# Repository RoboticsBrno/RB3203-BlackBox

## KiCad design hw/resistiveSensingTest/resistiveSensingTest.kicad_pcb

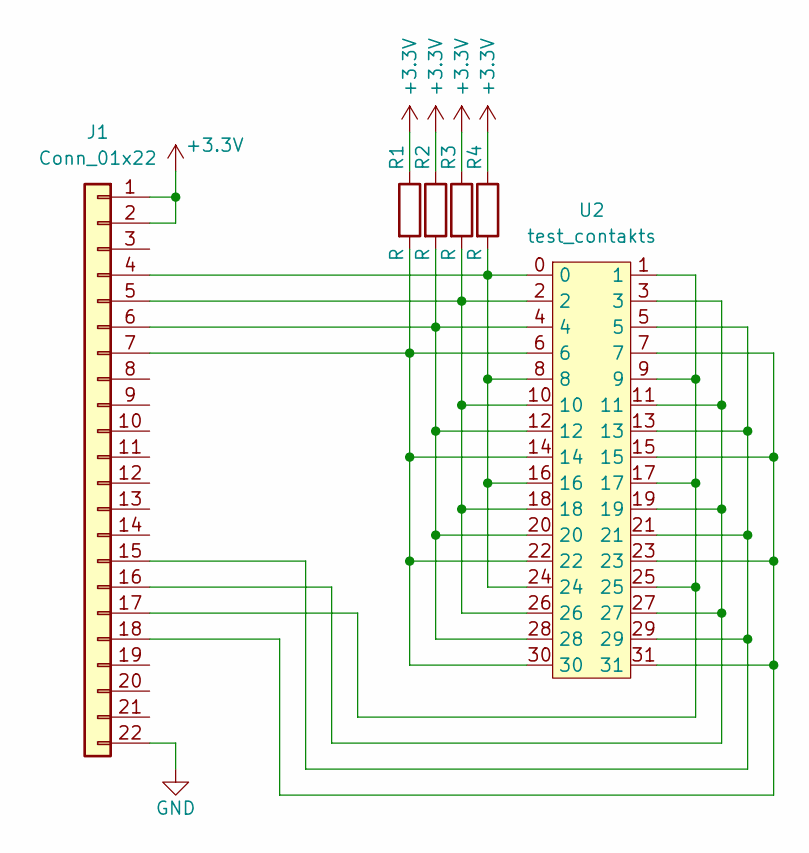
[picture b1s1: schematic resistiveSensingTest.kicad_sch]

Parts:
J1: Conn_01x22; PinHeader_1x22_P2.54mm_Vertical
R1, R2, R3, R4: R; R_1206_3216Metric_Pad1.30x1.75mm_HandSolder
U2: test_contakts

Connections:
+3.3V: J1.1, J1.2, R1.1, R2.1, R3.1, R4.1
GND: J1.22
unnamed: J1.7, R1.2, U2.6, U2.14, U2.22, U2.30
unnamed: J1.6, R2.2, U2.4, U2.12, U2.20, U2.28
unnamed: J1.5, R3.2, U2.2, U2.10, U2.18, U2.26
unnamed: J1.4, R4.2, U2.0, U2.8, U2.16, U2.24
unnamed: J1.17, U2.1, U2.9, U2.17, U2.25
unnamed: J1.16, U2.3, U2.11, U2.19, U2.27
unnamed: J1.15, U2.5, U2.13, U2.21, U2.29
unnamed: J1.18, U2.7, U2.15, U2.23, U2.31

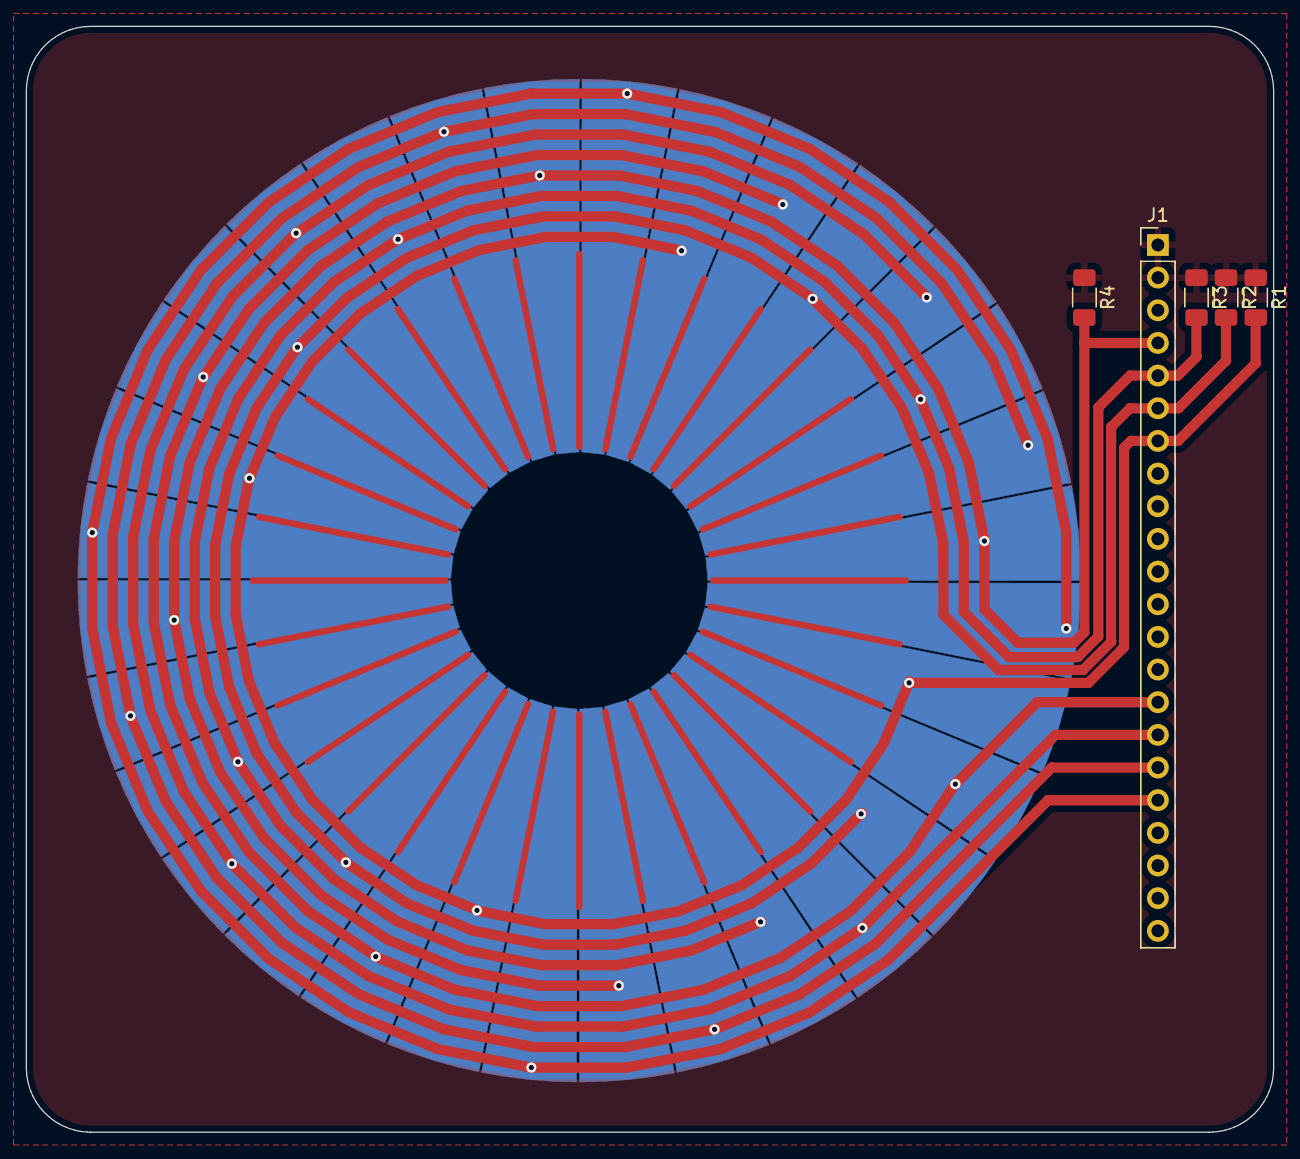
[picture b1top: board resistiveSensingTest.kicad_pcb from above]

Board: 2 copper layers, 97.0 x 86.0 mm, 6 parts (1 on the bottom side), 9 nets.

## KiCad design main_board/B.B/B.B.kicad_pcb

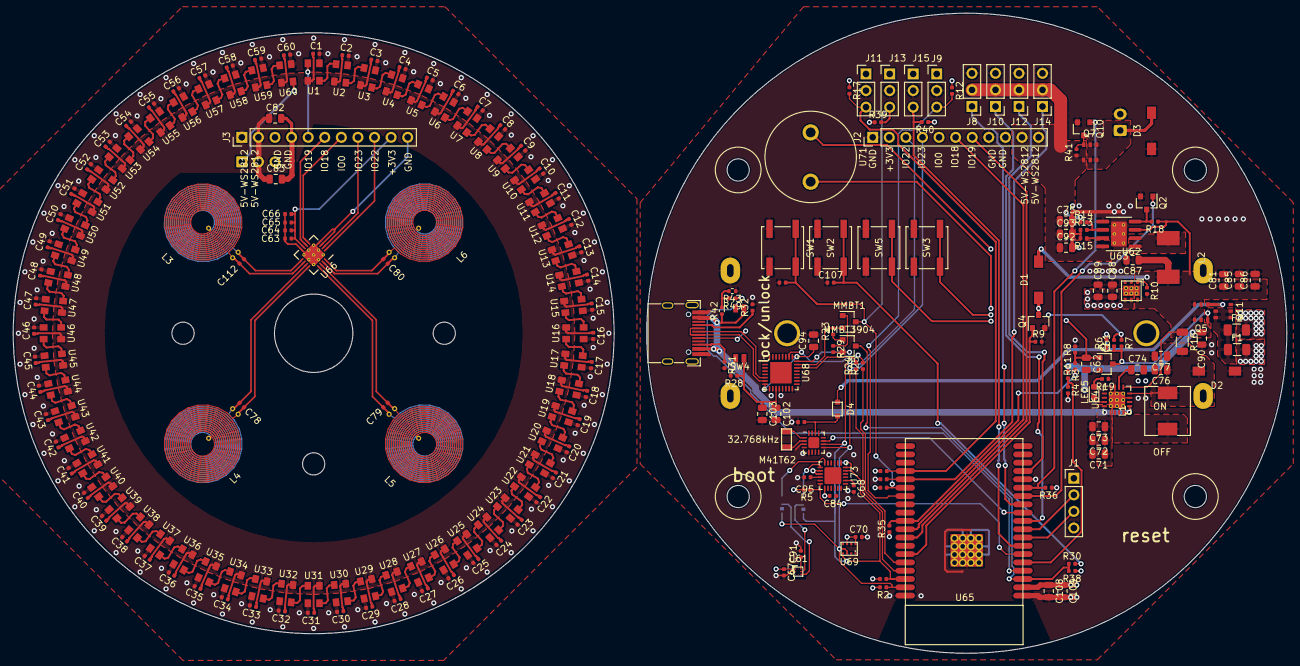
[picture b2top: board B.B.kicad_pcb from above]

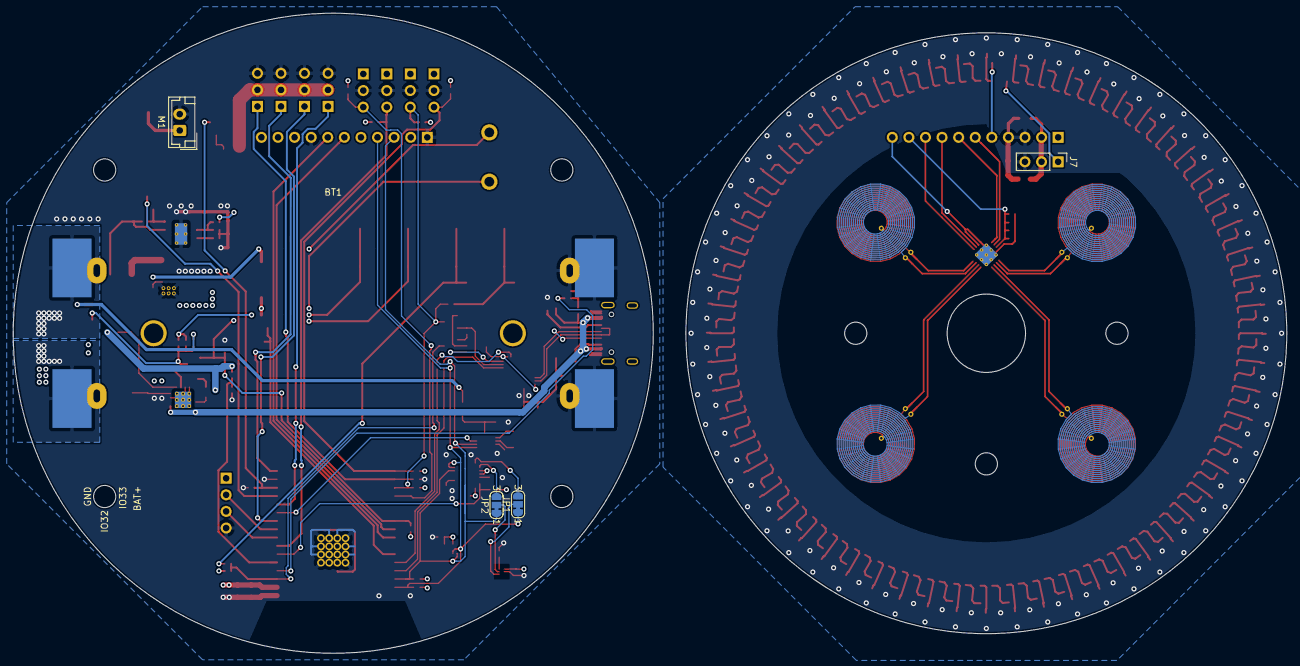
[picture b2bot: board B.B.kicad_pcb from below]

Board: 4 copper layers, 195.0 x 98.0 mm, 258 parts (5 on the bottom side), 152 nets.

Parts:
BT1: Battery_Cell; 18650-holder
C1, C2, C3, C4, C5, C6, C7, C8, C9, C10, C11, C12, C13, C14, C15, C16, C17, C18, C19, C20, C21, C22, C23, C24, C25, C26, C27, C28, C29, C30, C31, C32, C33, C34, C35, C36, C37, C38, C39, C40, C41, C42, C43, C44, C45, C46, C47, C48, C49, C50, C51, C52, C53, C54, C55, C56, C57, C58, C59, C60: 220nf; C_0402_1005Metric
C61, C66: 1uf; C_0402_1005Metric
C62, C89: 2.2uf; C_0805_2012Metric
C63, C64: 10nf; C_0402_1005Metric
C65, C95: 0.1uf; R_0402_1005Metric
C67, C68: 2.2uf; C_0402_1005Metric
C69, C70, C84: 1uf; R_0402_1005Metric
C71, C72, C73, C75, C86, C90, C92, C93: 22uf; C_0805_2012Metric
C74, C76, C81, C94, C102, C108: 0.1uf; C_0805_2012Metric
C77, C82, C83, C85, C88, C103, C109: 10uf; C_0805_2012Metric
C78, C79, C80, C112: 1000pf; C_0402_1005Metric
C87: 4.7uf; C_0805_2012Metric
C91: 4.7uf; C_0402_1005Metric
C104, C107: 100nf; C_0402_1005Metric
D1, D2, D3: SS54; DO-214AC
D4: D; SOD-323
F1, F2: Polyfuse; L_1206_3216Metric
J1: Conn_01x04; PinHeader_1x04_P2.54mm_Vertical
J2, J3: Conn_01x11; PinHeader_1x11_P2.54mm_Vertical
J5: USB_C_Receptacle_USB2.0; USB_C_Female-16Pin-HPJF
J7, J8, J9, J10, J11, J12, J13, J14, J15: Conn_01x03; PinHeader_1x03_P2.54mm_Vertical
JP1, JP2: Jumper_NC_Dual; SolderJumper-3_P1.3mm_Bridged12_RoundedPad1.0x1.5mm_NumberL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
L1: 22u; SL00630H
L2: 2.2uH; MWSA0603_6.6x7.1x3.0
L3, L4, L5, L6: L; coil
LED5: BLUE; LED_0603_1608Metric
M1: Motor_DC; JST_EH_B2B-EH-A_1x02_P2.50mm_Vertical
MMBT1, MMBT3904: Q_NPN_BCE; SOT-23
Q1, Q2, Q4, Q10: 2N7002; SOT-23
Q5, Q7, Q11: SI3447CDV; TSOP-6_1.5x3.0x0.95P
R1, R2, R13, R43: 7.5k; R_0402_1005Metric
R3, R7, R8, R28: 1M; R_0402_1005Metric
R4: 300k; C_0402_1005Metric
R5, R12, R17, R23, R29, R33, R34, R35, R36, R37, R38, R39, R40: 12k; R_0402_1005Metric
R6, R10, R18, R41: 100k; R_0402_1005Metric
R9: 47k; R_0402_1005Metric
R11, R24, R25, R49: 220; R_0402_1005Metric
R14, R15: 56k; R_0402_1005Metric
R16: 75m; R_1206_3216Metric
R19: 1k; R_0402_1005Metric
R20, R30: 470; R_0402_1005Metric
R31, R32, R42: 5.1k; R_0402_1005Metric
SW1, SW2, SW3, SW5: SW_DIP_x01; SW_Push_1P1T_NO_CK_KSC6xxJ
SW4: SW_DIP_x02; SW-SMD-4
U1, U2, U3, U4, U5, U6, U7, U8, U9, U10, U11, U12, U13, U14, U15, U16, U17, U18, U19, U20, U21, U22, U23, U24, U25, U26, U27, U28, U29, U30, U31, U32, U33, U34, U35, U36, U37, U38, U39, U40, U41, U42, U43, U44, U45, U46, U47, U48, U49, U50, U51, U52, U53, U54, U55, U56, U57, U58, U59, U60: WS2812
U61: QMC6310
U62: NCP708; UDFN6_3x3
U63: FP6276; SOIC-8-1EP_3.9x4.9mm_P1.27mm_EP2.41x3.81mm_ThermalVias
U64: TP5100; QFN-16-1EP_4x4mm_P0.65mm_EP2.5x2.5mm_ThermalVias
U65: ESP32-WROVER
U66: LDC1314; WQFN-16-1EP_4x4mm_P0.5mm_EP2.6x2.6mm_ThermalVias
U67: M41T62; QFN-16-1EP_3x3mm_P0.5mm_EP1.7x1.7mm
U68: FT232RQ; QFN-32-1EP_5x5mm_P0.5mm_EP3.3x3.3mm
U69: SPL06; SMD-8_2x2.5x0.65P
U71: piezo
U73: MPU6050; QFN-24-1EP_4x4mm_P0.5mm_EP2.6x2.6mm
Y1: 32.768kHz; SMD-3215_2P

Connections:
+3V3: C67.1, C70.1, C84.1, C88.1, C89.1, C108.1, C109.1, J2.2, J9.1, J11.1, J13.1, J15.1, R1.2, R2.2, R5.2, R12.1, R17.1, R33.1, R35.1, R37.1, R38.1, R39.1, R40.1, U61.A1, U62.4, U62.5, U65.2, U69.6, U69.8, U73.8, U73.9, U73.13
+5V: C75.1, C92.1, C93.1, J2.10, J2.11, J8.2, J10.2, J12.2, J14.2, Q7.4, R14.1, R41.1, U63.8
/BAT+: D4.2, Q5.4, Q11.4, R6.2
/ESP3200/D+: J5.A6, J5.B6, U68.14
/ESP3200/D-: J5.A7, J5.B7, U68.15
/ESP3200/DTR: MMBT1.2, R23.2, U68.31
/ESP3200/EN: MMBT3904.3, R30.1, R38.2, U65.3
/ESP3200/IO0-up: J13.3, MMBT1.3, R20.1, R33.2, R39.2, U65.25
/ESP3200/IO2-down: J14.1, R34.2, U65.24
/ESP3200/IO4: J9.3, R12.2, U65.26
/ESP3200/IO5-up: R11.1, R35.2, U65.29
/ESP3200/IO12-down: Q10.1, R36.2, U65.14
/ESP3200/IO13: J12.1, U65.16
/ESP3200/IO14: Q2.1, U65.13
/ESP3200/IO15-up: J11.3, R17.2, R37.2, U65.23
/ESP3200/IO18: J2.6, U65.30
/ESP3200/IO19: J2.7, U65.31
/ESP3200/IO21: Q4.1, R9.1, U65.33
/ESP3200/IO22: J2.3, JP2.1, R1.1, U65.36, U67.10, U69.4, U73.23
/ESP3200/IO23: J2.4, JP1.1, R2.1, U65.37, U67.9, U69.3, U73.24
/ESP3200/IO25: J10.1, U65.10
/ESP3200/IO26: U65.11, U67.11
/ESP3200/IO27: J8.1, U65.12
/ESP3200/IO34: R5.1, U65.6, U73.12
/ESP3200/IO35: J15.3, R40.2, U65.7
/ESP3200/IO36: R49.1, U65.4
/ESP3200/IO39: R3.2, R4.1, U65.5
/ESP3200/RTS: MMBT3904.2, R29.2, U68.32
/ESP3200/RX-esp: R25.1, U65.34
/ESP3200/TX-esp: R24.1, U65.35
/expanz00/A9-RX: J1.3, U65.8
/expanz00/A9-TX: J1.2, U65.9
/next-board00/3V3: C63.1, C64.1, C65.1, C66.2, J3.10, U66.7
/next-board00/5V: C1.2, C2.2, C3.2, C4.2, C5.2, C6.2, C7.2, C8.2, C9.2, C10.2, C11.2, C12.2, C13.2, C14.2, C15.2, C16.2, C17.2, C18.2, C19.2, C20.2, C21.2, C22.2, C23.2, C24.2, C25.2, C26.2, C27.2, C28.2, C29.2, C30.2, C31.2, C32.2, C33.2, C34.2, C35.2, C36.2, C37.2, C38.2, C39.2, C40.2, C41.2, C42.2, C43.2, C44.2, C45.2, C46.2, C47.2, C48.2, C49.2, C50.2, C51.2, C52.2, C53.2, C54.2, C55.2, C56.2, C57.2, C58.2, C59.2, C60.2, C82.1, C83.1, J3.1, J3.2, J7.2, U1.1, U2.1, U3.1, U4.1, U5.1, U6.1, U7.1, U8.1, U9.1, U10.1, U11.1, U12.1, U13.1, U14.1, U15.1, U16.1, U17.1, U18.1, U19.1, U20.1, U21.1, U22.1, U23.1, U24.1, U25.1, U26.1, U27.1, U28.1, U29.1, U30.1, U31.1, U32.1, U33.1, U34.1, U35.1, U36.1, U37.1, U38.1, U39.1, U40.1, U41.1, U42.1, U43.1, U44.1, U45.1, U46.1, U47.1, U48.1, U49.1, U50.1, U51.1, U52.1, U53.1, U54.1, U55.1, U56.1, U57.1, U58.1, U59.1, U60.1
/next-board00/GND: C1.1, C2.1, C3.1, C4.1, C5.1, C6.1, C7.1, C8.1, C9.1, C10.1, C11.1, C12.1, C13.1, C14.1, C15.1, C16.1, C17.1, C18.1, C19.1, C20.1, C21.1, C22.1, C23.1, C24.1, C25.1, C26.1, C27.1, C28.1, C29.1, C30.1, C31.1, C32.1, C33.1, C34.1, C35.1, C36.1, C37.1, C38.1, C39.1, C40.1, C41.1, C42.1, C43.1, C44.1, C45.1, C46.1, C47.1, C48.1, C49.1, C50.1, C51.1, C52.1, C53.1, C54.1, C55.1, C56.1, C57.1, C58.1, C59.1, C60.1, C82.2, C83.2, J3.3, J3.4, J7.3, U1.3, U2.3, U3.3, U4.3, U5.3, U6.3, U7.3, U8.3, U9.3, U10.3, U11.3, U12.3, U13.3, U14.3, U15.3, U16.3, U17.3, U18.3, U19.3, U20.3, U21.3, U22.3, U23.3, U24.3, U25.3, U26.3, U27.3, U28.3, U29.3, U30.3, U31.3, U32.3, U33.3, U34.3, U35.3, U36.3, U37.3, U38.3, U39.3, U40.3, U41.3, U42.3, U43.3, U44.3, U45.3, U46.3, U47.3, U48.3, U49.3, U50.3, U51.3, U52.3, U53.3, U54.3, U55.3, U56.3, U57.3, U58.3, U59.3, U60.3
/next-board00/INT: J3.7, U66.5
/next-board00/LDC-GND: C63.2, C64.2, C65.2, C66.1, J3.11, U66.3, U66.4, U66.8, U66.17
/next-board00/SCL: J3.9, U66.1
/next-board00/SDA: J3.8, U66.2
/next-board00/SHUTDOWN: J3.6, U66.6
/next-board00/WS2812: J3.5, U1.4
/next-board00/WS281200/0-8: U8.2, U9.4
/next-board00/WS281200/1-8: U16.2, U17.4
/next-board00/WS281200/2-8: U24.2, U25.4
/next-board00/WS281200/3-8: U32.2, U33.4
/next-board00/WS281200/4-8: U40.2, U41.4
/next-board00/WS281200/5-8: U48.2, U49.4
/next-board00/WS281200/6-8: U56.2, U57.4
/next-board00/WS281200/DOUT: J7.1, U60.2
GND: BT1.2, BT1.4, C62.2, C67.2, C68.2, C69.2, C70.2, C71.2, C72.2, C73.2, C74.2, C75.2, C76.2, C77.2, C81.2, C84.2, C85.2, C86.2, C87.2, C88.2, C89.2, C90.2, C91.2, C92.2, C93.2, C94.2, C95.2, C102.2, C103.2, C104.1, C107.1, C108.2, C109.2, D2.2, D3.2, J1.4, J2.1, J2.8, J2.9, J5.A1, J5.A12, J5.B1, J5.B12, J8.3, J9.2, J10.3, J11.2, J12.3, J13.2, J14.3, J15.2, M1.2, Q1.2, Q2.2, Q4.2, Q10.2, Q11.3, R4.2, R8.2, R9.2, R13.1, R15.2, R19.1, R28.2, R31.2, R32.2, R34.1, R36.1, R43.1, SW1.1, SW2.1, SW3.1, SW5.1, U61.B1, U62.2, U62.7, U63.5, U63.9, U64.7, U64.11, U64.12, U64.17, U65.1, U65.15, U65.38, U65.39, U67.3, U67.5, U68.4, U68.17, U68.20, U68.24, U68.26, U69.1, U69.7, U73.1, U73.11, U73.18
LX: L2.2, U63.1, U63.2
unnamed: BT1.1, F2.2
unnamed: BT1.3, F1.2
unnamed: C61.1, Q1.3, Q5.3, R6.1, R7.2
unnamed: C61.2, R7.1, SW3.2
unnamed: C62.1, Q1.1, R8.1, R11.2, SW5.2
unnamed: C68.1, U73.20
unnamed: C69.1, D4.1, U67.14
unnamed: C74.1, U64.10
unnamed: C76.1, C77.1, D2.1, L1.2, R16.2, U64.8
unnamed: C78.1, L4.1, U66.12
unnamed: C78.2, L4.2, U66.11
unnamed: C79.1, L5.1, U66.14
unnamed: C79.2, L5.2, U66.13
unnamed: C80.1, L6.1, U66.16
unnamed: C80.2, L6.2, U66.15
unnamed: C91.1, U61.A3
unnamed: C94.1, U68.1, U68.16
unnamed: C95.1, U73.10
unnamed: C102.1, C103.1, R28.1, SW4.3, U68.19
unnamed: C104.2, R20.2, SW1.2
unnamed: C107.2, R30.2, SW2.2
unnamed: C112.1, L3.1, U66.10
unnamed: C112.2, L3.2, U66.9
unnamed: D1.2, Q4.3, U71.1
unnamed: D3.1, M1.1, Q7.1, Q7.2, Q7.5, Q7.6
unnamed: F1.1, F2.1, Q11.1, Q11.2, Q11.5, Q11.6
unnamed: J5.A5, R32.1
unnamed: J5.B5, R31.1
unnamed: JP1.2, U61.C3
unnamed: JP1.3, U73.6
unnamed: JP2.2, U61.B3
unnamed: JP2.3, U73.7
unnamed: L1.1, U64.2, U64.3
unnamed: LED5.1, U64.15
unnamed: LED5.2, R19.2
unnamed: MMBT1.1, R29.1
unnamed: MMBT3904.1, R23.1
unnamed: Q2.3, R18.2, U63.4
unnamed: Q7.3, Q10.3, R41.2
unnamed: R10.1, U62.1
unnamed: R13.2, R14.2, U63.6
unnamed: R15.1, U63.7
unnamed: R24.2, U68.30
unnamed: R25.2, U68.2
unnamed: R42.2, R43.2, R49.2
unnamed: U1.2, U2.4
unnamed: U2.2, U3.4
unnamed: U3.2, U4.4
unnamed: U4.2, U5.4
unnamed: U5.2, U6.4
unnamed: U6.2, U7.4
unnamed: U7.2, U8.4
unnamed: U10.2, U11.4
unnamed: U9.2, U10.4
unnamed: U11.2, U12.4
unnamed: U12.2, U13.4
unnamed: U13.2, U14.4
unnamed: U14.2, U15.4
unnamed: U15.2, U16.4
unnamed: U17.2, U18.4
unnamed: U18.2, U19.4
unnamed: U19.2, U20.4
unnamed: U20.2, U21.4
unnamed: U21.2, U22.4
unnamed: U22.2, U23.4
unnamed: U23.2, U24.4
unnamed: U25.2, U26.4
unnamed: U26.2, U27.4
unnamed: U27.2, U28.4
unnamed: U28.2, U29.4
unnamed: U29.2, U30.4
unnamed: U30.2, U31.4
unnamed: U31.2, U32.4
unnamed: U33.2, U34.4
unnamed: U34.2, U35.4
unnamed: U35.2, U36.4
unnamed: U36.2, U37.4
unnamed: U37.2, U38.4
unnamed: U38.2, U39.4
unnamed: U39.2, U40.4
unnamed: U41.2, U42.4
unnamed: U42.2, U43.4
unnamed: U43.2, U44.4
unnamed: U44.2, U45.4
unnamed: U45.2, U46.4
unnamed: U46.2, U47.4
unnamed: U47.2, U48.4
unnamed: U49.2, U50.4
unnamed: U50.2, U51.4
unnamed: U51.2, U52.4
unnamed: U52.2, U53.4
unnamed: U53.2, U54.4
unnamed: U54.2, U55.4
unnamed: U55.2, U56.4
unnamed: U57.2, U58.4
unnamed: U58.2, U59.4
unnamed: U59.2, U60.4
unnamed: U67.1, Y1.1
unnamed: U67.2, Y1.2
VCC: C81.1, C85.1, C86.1, C87.1, C90.1, D1.1, J1.1, L2.1, Q5.1, Q5.2, Q5.5, Q5.6, R3.1, R10.2, R16.1, R18.1, U62.6, U63.3, U64.9, U71.2
VIN: C71.1, C72.1, C73.1, J5.A4, J5.A9, J5.B4, J5.B9, R42.1, SW4.2, U64.1, U64.4, U64.5, U64.16

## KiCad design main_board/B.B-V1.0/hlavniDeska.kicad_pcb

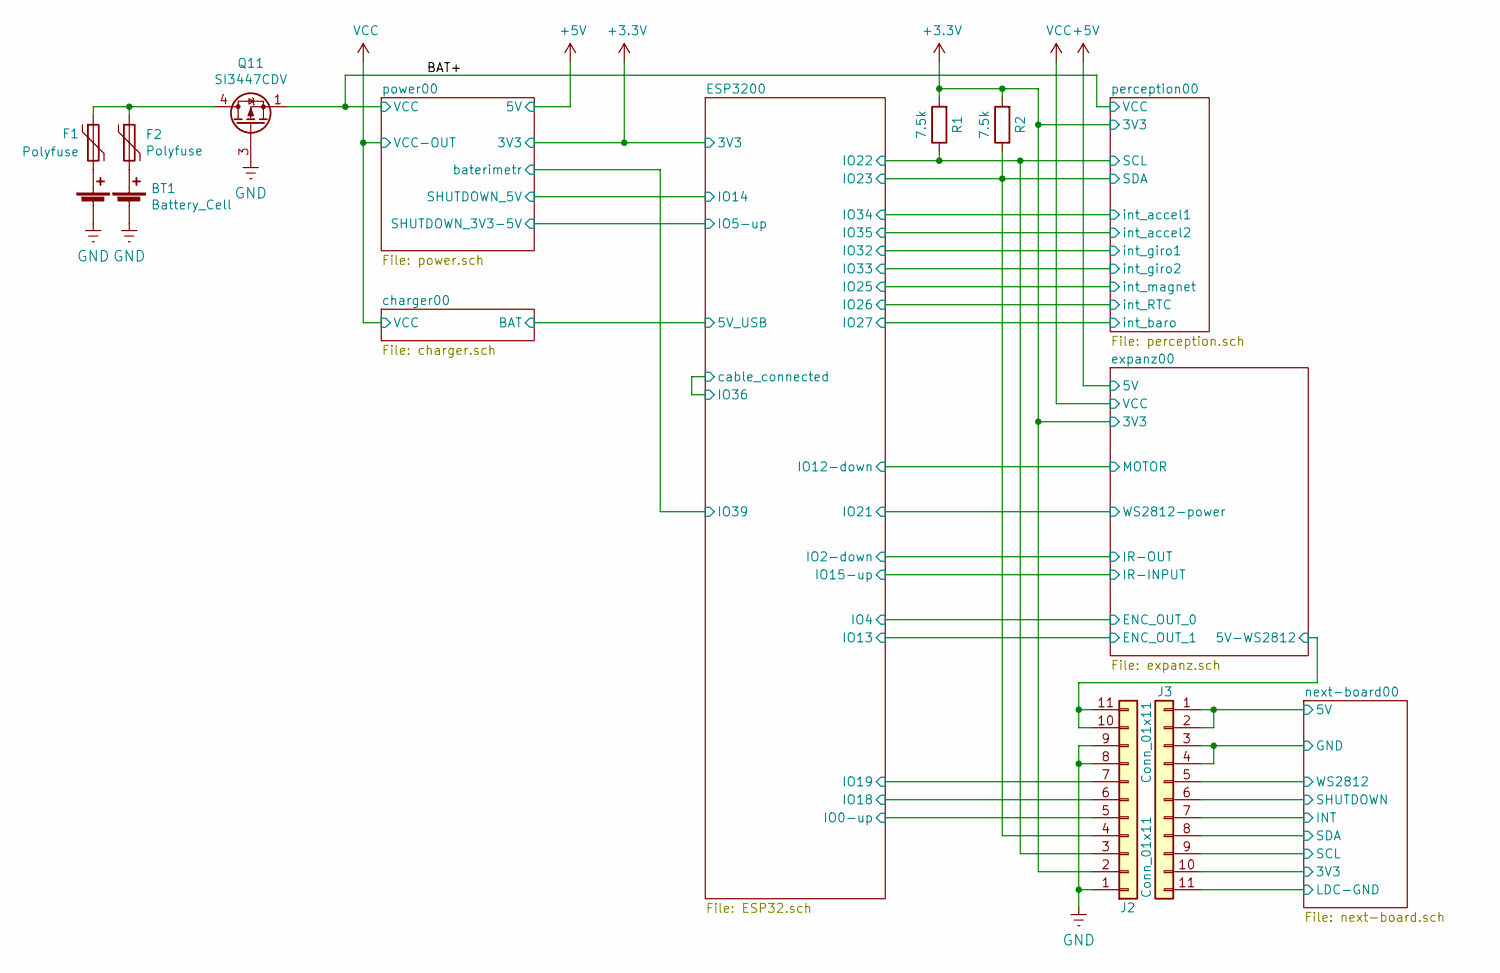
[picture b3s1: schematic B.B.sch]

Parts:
BT1: Battery_Cell; 18650-holder
F1, F2: Polyfuse; L_1206_3216Metric; LCSC C20988
J2, J3: Conn_01x11; PinHeader_1x11_P2.54mm_Vertical
Q11: SI3447CDV; TSOP-6_1.5x3.0x0.95P; LCSC C144884
R1, R2: 7.5k; R_0402_1005Metric; LCSC C25918

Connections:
+3V3: J2.2, R1.2, R2.2; also elsewhere on the board
/BAT+: Q11.1 (S), Q11.2, Q11.5, Q11.6; also elsewhere on the board
/ESP3200/IO0-up: J2.5; also elsewhere on the board
/ESP3200/IO18: J2.6; also elsewhere on the board
/ESP3200/IO19: J2.7; also elsewhere on the board
/ESP3200/IO22: J2.3, R1.1; also elsewhere on the board
/ESP3200/IO23: J2.4, R2.1; also elsewhere on the board
/expanz00/5V-WS2812: J2.10, J2.11; also elsewhere on the board
GND: BT1.2 (-), BT1.4 (-), J2.1, J2.8, J2.9, Q11.3 (G); also elsewhere on the board
unnamed: BT1.1 (+), F2.2
unnamed: BT1.3 (+), F1.2
unnamed: F1.1, F2.1, Q11.4 (D)
unnamed: J3.1, J3.2
unnamed: J3.3, J3.4

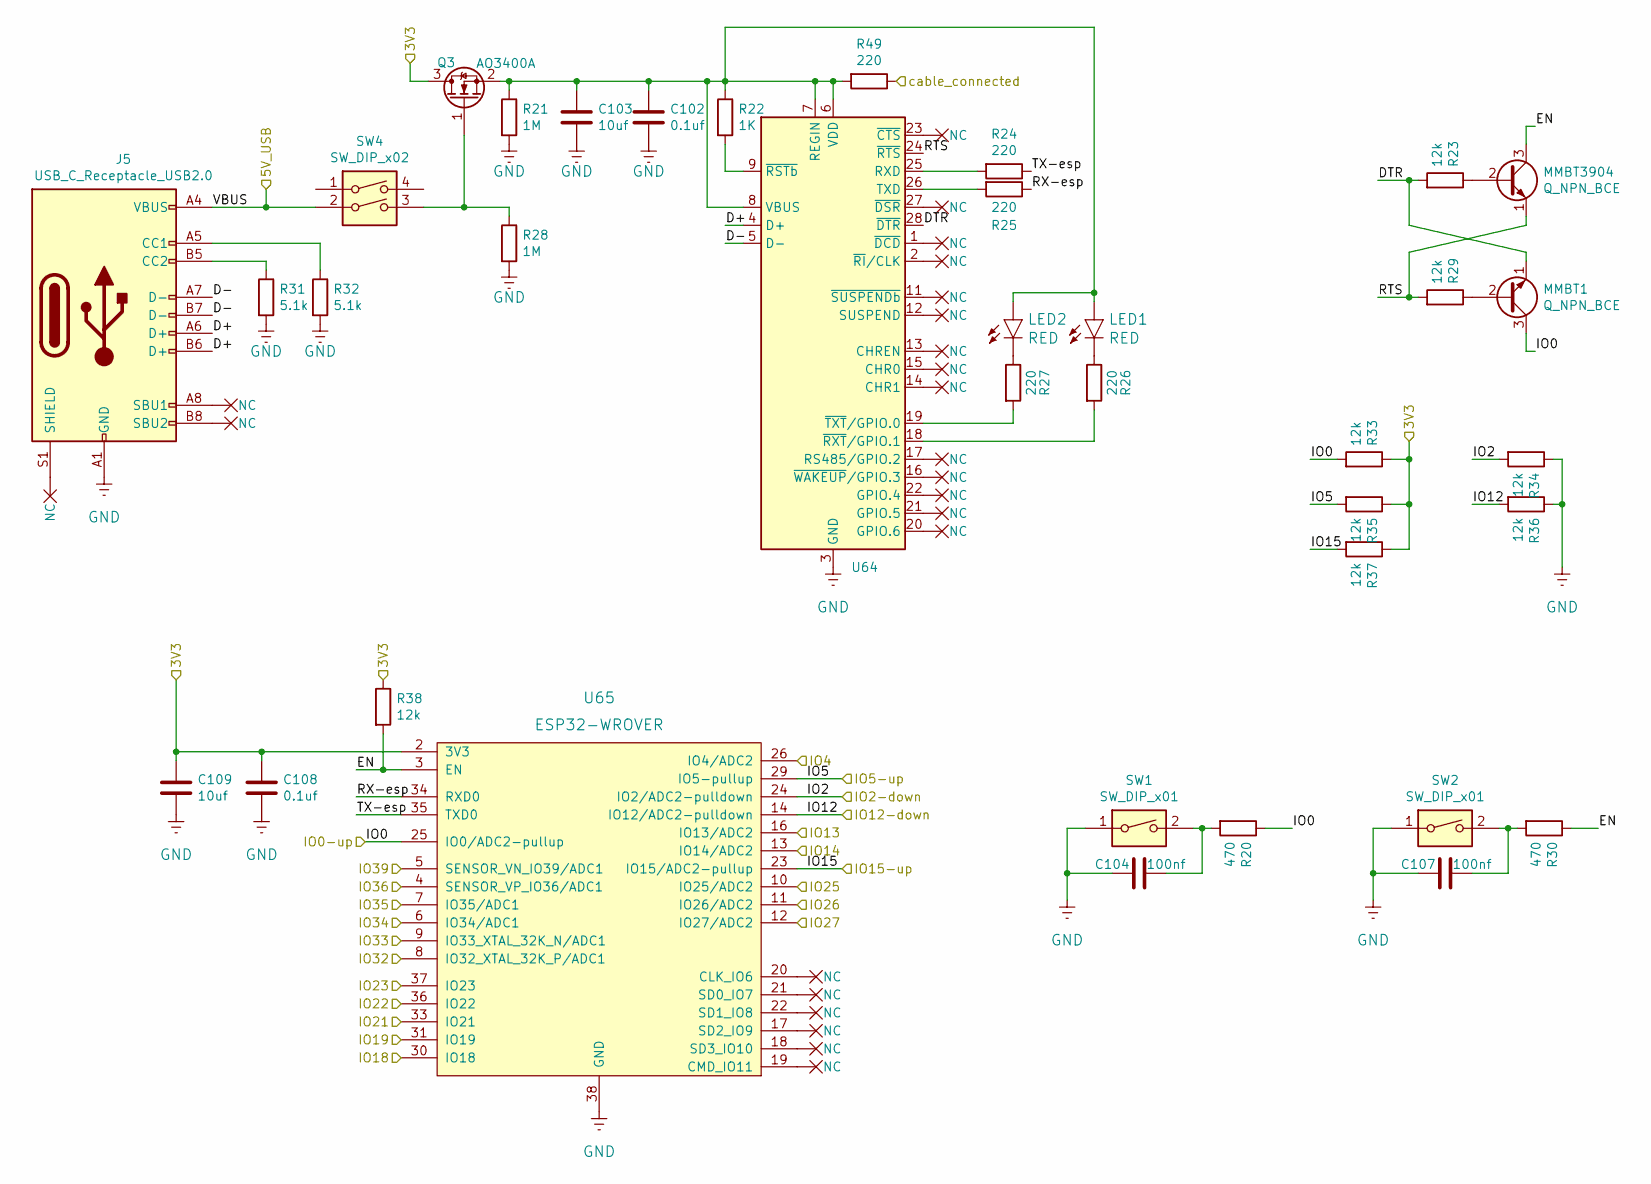
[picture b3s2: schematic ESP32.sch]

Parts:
C102, C108: 0.1uf; C_0805_2012Metric; LCSC C49678
C103, C109: 10uf; C_0805_2012Metric; LCSC C15850
C104, C107: 100nf; C_0402_1005Metric; LCSC C1525
J5: USB_C_Receptacle_USB2.0; USB_C_Female-16Pin-HPJF
LED1, LED2: RED; LED_0603_1608Metric; LCSC C2286
MMBT1, MMBT3904: Q_NPN_BCE; SOT-23; LCSC C20526
Q3: AO3400A; SOT-23; LCSC C20917
R20, R30: 470; R_0402_1005Metric; LCSC C25117
R21, R28: 1M; R_0402_1005Metric; LCSC C26083
R22: 1K; R_0402_1005Metric; LCSC C11702
R23, R29, R33, R34, R35, R36, R37, R38: 12k; R_0402_1005Metric; LCSC C25752
R24, R25, R26, R27, R49: 220; R_0402_1005Metric; LCSC C25092
R31, R32: 5.1k; R_0402_1005Metric; LCSC C25905
SW1, SW2: SW_DIP_x01; SW_Push_1P1T_NO_CK_KSC6xxJ; LCSC C318889
SW4: SW_DIP_x02; SW-SMD-4; LCSC C319052
U64: CP2102N-A01-GQFN28; QFN-28-1EP_5x5mm_P0.5mm_EP3.35x3.35mm; LCSC C105167
U65: ESP32-WROVER; LCSC C503591

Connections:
+3V3: C108.1, C109.1, Q3.3 (D), R33.1, R35.1, R37.1, R38.1, U65.2 (3V3); also elsewhere on the board
/ESP3200/5V_USB: J5.A4 (VBUS), J5.A9 (VBUS), J5.B4 (VBUS), J5.B9 (VBUS), SW4.2; also elsewhere on the board
/ESP3200/D+: J5.A6 (D+), J5.B6 (D+), U64.4 (D+)
/ESP3200/D-: J5.A7 (D-), J5.B7 (D-), U64.5 (D-)
/ESP3200/DTR: MMBT1.1 (E), R23.2, U64.28 (~DTR)
/ESP3200/EN: MMBT3904.3 (C), R30.1, R38.2, U65.3 (EN)
/ESP3200/IO0-up: MMBT1.3 (C), R20.1, R33.2, U65.25 (IO0/ADC2-pullup); also elsewhere on the board
/ESP3200/IO2-down: R34.2, U65.24 (IO2/ADC2-pulldown); also elsewhere on the board
/ESP3200/IO5-up: R35.2, U65.29 (IO5-pullup); also elsewhere on the board
/ESP3200/IO12-down: R36.2, U65.14 (IO12/ADC2-pulldown); also elsewhere on the board
/ESP3200/IO14: U65.13 (IO14/ADC2); also elsewhere on the board
/ESP3200/IO15-up: R37.2, U65.23 (IO15/ADC2-pullup); also elsewhere on the board
/ESP3200/IO18: U65.30 (IO18); also elsewhere on the board
/ESP3200/IO19: U65.31 (IO19); also elsewhere on the board
/ESP3200/IO21: U65.33 (IO21); also elsewhere on the board
/ESP3200/IO22: U65.36 (IO22); also elsewhere on the board
/ESP3200/IO23: U65.37 (IO23); also elsewhere on the board
/ESP3200/IO25: U65.10 (IO25/ADC2); also elsewhere on the board
/ESP3200/IO26: U65.11 (IO26/ADC2); also elsewhere on the board
/ESP3200/IO27: U65.12 (IO27/ADC2); also elsewhere on the board
/ESP3200/IO32: U65.8 (IO32_XTAL_32K_P/ADC1); also elsewhere on the board
/ESP3200/IO33: U65.9 (IO33_XTAL_32K_N/ADC1); also elsewhere on the board
/ESP3200/IO34: U65.6 (IO34/ADC1); also elsewhere on the board
/ESP3200/IO35: U65.7 (IO35/ADC1); also elsewhere on the board
/ESP3200/IO36: R49.1, U65.4 (SENSOR_VP_IO36/ADC1)
/ESP3200/IO39: U65.5 (SENSOR_VN_IO39/ADC1); also elsewhere on the board
/ESP3200/RTS: MMBT3904.1 (E), R29.2, U64.24 (~RTS)
/ESP3200/RX-esp: R25.1, U65.34 (RXD0)
/ESP3200/TX-esp: R24.1, U65.35 (TXD0)
/expanz00/ENC_OUT_0: U65.26 (IO4/ADC2); also elsewhere on the board
/expanz00/ENC_OUT_1: U65.16 (IO13/ADC2); also elsewhere on the board
GND: C102.2, C103.2, C104.1, C107.1, C108.2, C109.2, J5.A1 (GND), J5.A12 (GND), J5.B1 (GND), J5.B12 (GND), R21.2, R28.2, R31.2, R32.2, R34.1, R36.1, SW1.1, SW2.1, U64.3 (GND), U64.29 (GND), U65.1 (GND), U65.15 (GND), U65.38 (GND), U65.39 (GND); also elsewhere on the board
unnamed: C102.1, C103.1, LED1.2 (A), LED2.2 (A), Q3.2 (S), R21.1, R22.1, R49.2, U64.6 (VDD), U64.7 (REGIN), U64.8 (VBUS)
unnamed: C104.2, R20.2, SW1.2
unnamed: C107.2, R30.2, SW2.2
unnamed: J5.A5 (CC1), R32.1
unnamed: J5.B5 (CC2), R31.1
unnamed: LED1.1 (C), R26.1
unnamed: LED2.1 (C), R27.1
unnamed: MMBT1.2 (B), R29.1
unnamed: MMBT3904.2 (B), R23.1
unnamed: Q3.1 (G), R28.1, SW4.3
unnamed: R22.2, U64.9 (~RSTb)
unnamed: R24.2, U64.25 (RXD)
unnamed: R25.2, U64.26 (TXD)
unnamed: R26.2, U64.18 (~RXT~/GPIO.1)
unnamed: R27.2, U64.19 (~TXT~/GPIO.0)

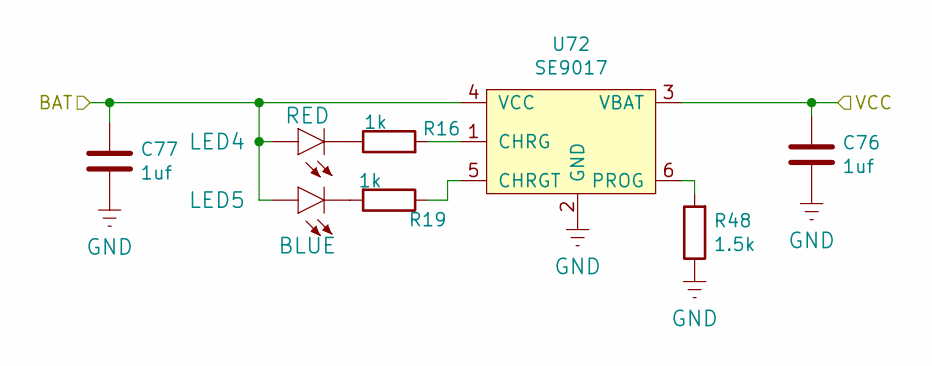
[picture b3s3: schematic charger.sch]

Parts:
C76, C77: 1uf; R_0402_1005Metric; LCSC C52923
LED4: RED; LED_0603_1608Metric; LCSC C2286
LED5: BLUE; LED_0603_1608Metric; LCSC C72041
R16, R19: 1k; R_0402_1005Metric; LCSC C11702
R48: 1.5k; R_0603_1608Metric; LCSC C22843
U72: SE9017; SOT-23-6; LCSC C115751

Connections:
/ESP3200/5V_USB: C77.1, LED4.2 (A), LED5.2 (A), U72.4 (VCC); also elsewhere on the board
GND: C76.2, C77.2, R48.1, U72.2 (GND); also elsewhere on the board
unnamed: LED4.1 (C), R16.1
unnamed: LED5.1 (C), R19.2
unnamed: R16.2, U72.1 (CHRG)
unnamed: R19.1, U72.5 (CHRGT)
unnamed: R48.2, U72.6 (PROG)
VCC: C76.1, U72.3 (VBAT); also elsewhere on the board

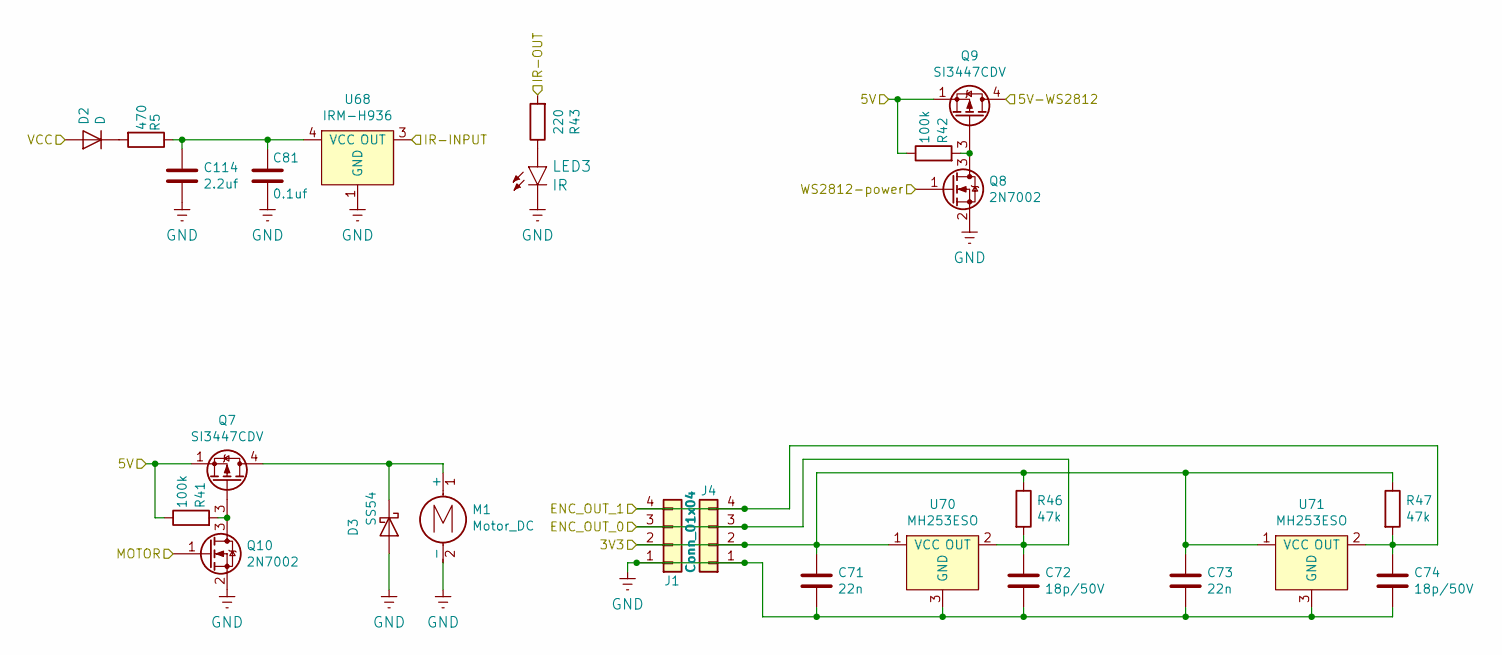
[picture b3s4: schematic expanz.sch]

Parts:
C71, C73: 22n; C_0402_1005Metric; LCSC C1532
C72, C74: 18p/50V; C_0402_1005Metric; LCSC C1549
C81: 0.1uf; R_0402_1005Metric; LCSC C1525
C114: 2.2uf; C_0805_2012Metric; LCSC C49217
D2: D; SOD-323; LCSC C109204
D3: SS54; DO-214AC; LCSC C22452
J1, J4: Conn_01x04; PinSocket_1x04_P2.54mm_Vertical
LED3: IR; LED_0603_1608Metric; LCSC C142316
M1: Motor_DC; PinHeader_1x02_P1.00mm_Vertical
Q7, Q9: SI3447CDV; TSOP-6_1.5x3.0x0.95P; LCSC C144884
Q8, Q10: 2N7002; SOT-23; LCSC C8545
R5: 470; R_0402_1005Metric; LCSC C25117
R41, R42: 100k; R_0402_1005Metric; LCSC C25741
R43: 220; R_0402_1005Metric; LCSC C25092
R46, R47: 47k; R_0402_1005Metric; LCSC C25792
U68: IRM-H936; SMD-4_4.0x5.0x2.54P; LCSC C264266
U70, U71: MH253ESO; SOT-23; LCSC C114369

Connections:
+3V3: C71.1, C73.1, J1.2, J4.2, R46.1, R47.1, U70.1 (VCC), U71.1 (VCC); also elsewhere on the board
+5V: Q7.1 (S), Q7.2, Q7.5, Q7.6, Q9.1 (S), Q9.2, Q9.5, Q9.6, R41.1, R42.1; also elsewhere on the board
/ESP3200/IO2-down: R43.2; also elsewhere on the board
/ESP3200/IO12-down: Q10.1 (G); also elsewhere on the board
/ESP3200/IO15-up: U68.3 (OUT); also elsewhere on the board
/ESP3200/IO21: Q8.1 (G); also elsewhere on the board
/expanz00/5V-WS2812: Q9.4 (D); also elsewhere on the board
/expanz00/ENC_OUT_0: C72.1, J1.3, J4.3, R46.2, U70.2 (OUT); also elsewhere on the board
/expanz00/ENC_OUT_1: C74.1, J1.4, J4.4, R47.2, U71.2 (OUT); also elsewhere on the board
GND: C71.2, C72.2, C73.2, C74.2, C81.2, C114.2, D3.2 (A), J1.1, J4.1, LED3.1 (C), M1.2 (-), Q8.2 (S), Q10.2 (S), U68.1 (GND), U68.2 (GND), U70.3 (GND), U71.3 (GND); also elsewhere on the board
unnamed: C81.1, C114.1, R5.1, U68.4 (VCC)
unnamed: D2.1 (K), R5.2
unnamed: D3.1 (K), M1.1 (+), Q7.4 (D)
unnamed: LED3.2 (A), R43.1
unnamed: Q8.3 (D), Q9.3 (G), R42.2
unnamed: Q7.3 (G), Q10.3 (D), R41.2
VCC: D2.2 (A); also elsewhere on the board

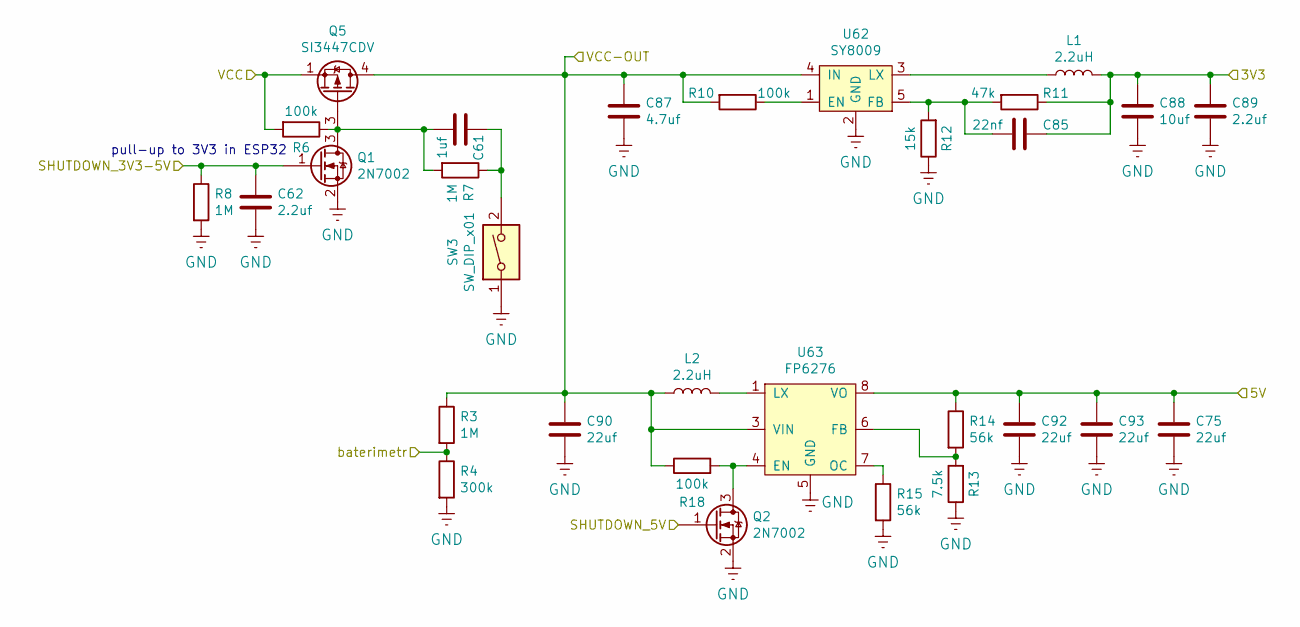
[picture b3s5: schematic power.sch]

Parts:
C61: 1uf; C_0402_1005Metric; LCSC C52923
C62, C89: 2.2uf; C_0805_2012Metric; LCSC C49217
C75, C90, C92, C93: 22uf; C_0805_2012Metric; LCSC C45783
C85: 22nf; C_0402_1005Metric; LCSC C1555
C87: 4.7uf; C_0805_2012Metric; LCSC C1779
C88: 10uf; C_0805_2012Metric; LCSC C15850
L1, L2: 2.2uH; MWSA0603_6.6x7.1x3.0; LCSC C351096
Q1, Q2: 2N7002; SOT-23; LCSC C8545
Q5: SI3447CDV; TSOP-6_1.5x3.0x0.95P; LCSC C144884
R3, R7, R8: 1M; R_0402_1005Metric; LCSC C26083
R4: 300k; C_0402_1005Metric; LCSC C25774
R6, R10, R18: 100k; R_0402_1005Metric; LCSC C25741
R11: 47k; R_0402_1005Metric; LCSC C25792
R12: 15k; R_0402_1005Metric; LCSC C25756
R13: 7.5k; R_0402_1005Metric; LCSC C25918
R14, R15: 56k; R_0402_1005Metric; LCSC C25796
SW3: SW_DIP_x01; SW_Push_1P1T_NO_CK_KSC6xxJ; LCSC C318889
U62: SY8009; SOT-23-5; LCSC C131989
U63: FP6276; SOP-8_3.76x4.96mm_P1.27mm; LCSC C82652

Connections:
+3V3: C85.1, C88.1, C89.1, L1.2, R11.1; also elsewhere on the board
+5V: C75.1, C92.1, C93.1, R14.1, U63.8 (VO); also elsewhere on the board
/BAT+: Q5.1 (S), Q5.2, Q5.5, Q5.6, R6.2; also elsewhere on the board
/ESP3200/IO5-up: C62.1, Q1.1 (G), R8.1; also elsewhere on the board
/ESP3200/IO14: Q2.1 (G); also elsewhere on the board
/ESP3200/IO39: R3.2, R4.1; also elsewhere on the board
GND: C62.2, C75.2, C87.2, C88.2, C89.2, C90.2, C92.2, C93.2, Q1.2 (S), Q2.2 (S), R4.2, R8.2, R12.1, R13.1, R15.2, SW3.1, U62.2 (GND), U63.5 (GND); also elsewhere on the board
LX: L2.2, U63.1 (LX), U63.2 (LX)
unnamed: C61.1, Q1.3 (D), Q5.3 (G), R6.1, R7.2
unnamed: C61.2, R7.1, SW3.2
unnamed: C85.2, R11.2, R12.2, U62.5 (FB)
unnamed: L1.1, U62.3 (LX)
unnamed: Q2.3 (D), R18.2, U63.4 (EN)
unnamed: R10.1, U62.1 (EN)
unnamed: R13.2, R14.2, U63.6 (FB)
unnamed: R15.1, U63.7 (OC)
VCC: C87.1, C90.1, L2.1, Q5.4 (D), R3.1, R10.2, R18.1, U62.4 (IN), U63.3 (VIN); also elsewhere on the board

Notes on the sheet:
pull-up to 3V3 in ESP32

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

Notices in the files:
main_board/B.B-V1.1/B.B.sch:
Released under the Creative Commons Attribution-ShareAlike 4.0 License
https://creativecommons.org/licenses/by-sa/4.0
